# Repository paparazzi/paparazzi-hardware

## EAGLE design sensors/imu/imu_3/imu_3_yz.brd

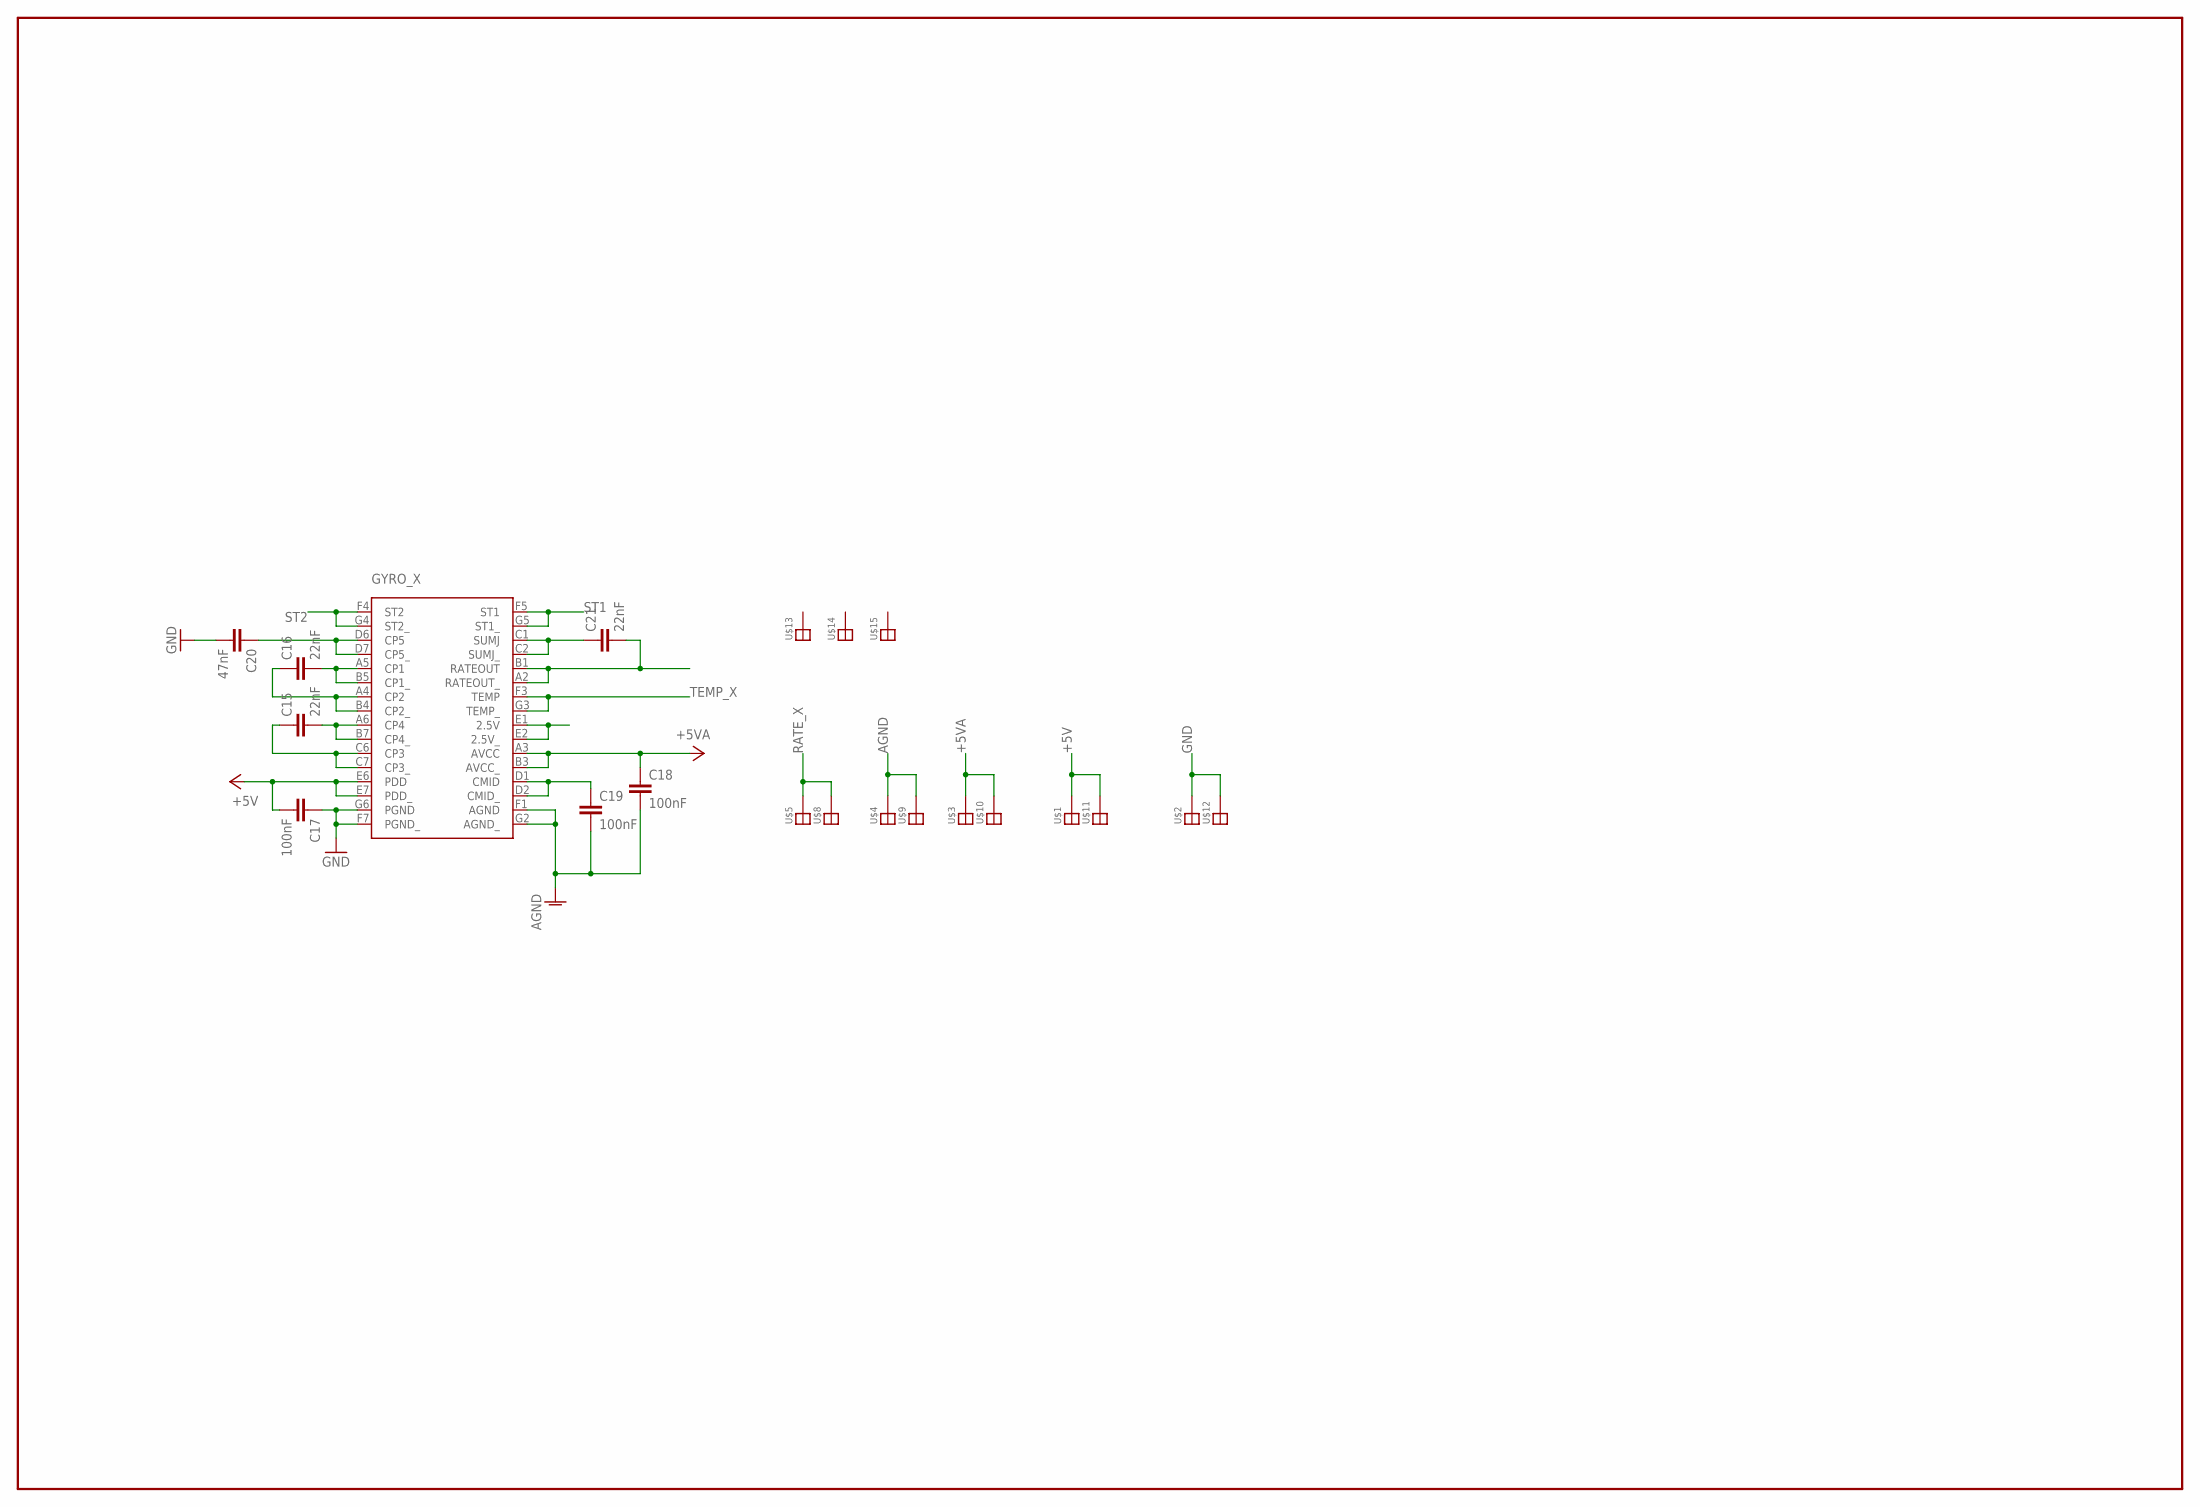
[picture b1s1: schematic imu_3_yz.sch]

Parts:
C15, C16, C21: 22nF; C0402K
C17, C18, C19: 100nF; C0402K
C20: 47nF; C0402K
GYRO_X: ADXR; BC-32
U$1, U$2, U$3, U$4, U$5, U$8, U$9, U$10, U$11, U$12, U$13, U$14, U$15: SOLDER_PAD

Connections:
+5V: C17.2, GYRO_X.E6 (PDD), GYRO_X.E7 (PDD_), U$1.P$1, U$11.P$1
+5VA: C18.1, GYRO_X.A3 (AVCC), GYRO_X.B3 (AVCC_), U$3.P$1, U$10.P$1
AGND: C18.2, C19.2, GYRO_X.F1 (AGND), GYRO_X.G2 (AGND_), U$4.P$1, U$9.P$1
GND: C17.1, C20.2, GYRO_X.F7 (PGND_), GYRO_X.G6 (PGND), U$2.P$1, U$12.P$1
unnamed: C21.1, GYRO_X.C1 (SUMJ), GYRO_X.C2 (SUMJ_)
unnamed: C15.1, GYRO_X.C6 (CP3), GYRO_X.C7 (CP3_)
unnamed: C20.1, GYRO_X.D6 (CP5), GYRO_X.D7 (CP5_)
unnamed: C16.2, GYRO_X.A5 (CP1), GYRO_X.B5 (CP1_)
unnamed: C16.1, GYRO_X.A4 (CP2), GYRO_X.B4 (CP2_)
unnamed: C15.2, GYRO_X.A6 (CP4), GYRO_X.B7 (CP4_)
unnamed: GYRO_X.E1 (2.5V), GYRO_X.E2 (2.5V_)
unnamed: C19.1, GYRO_X.D1 (CMID), GYRO_X.D2 (CMID_)
RATE_X: C21.2, GYRO_X.A2 (RATEOUT_), GYRO_X.B1 (RATEOUT), U$5.P$1, U$8.P$1
ST1: GYRO_X.F5 (ST1), GYRO_X.G5 (ST1_)
ST2: GYRO_X.F4 (ST2), GYRO_X.G4 (ST2_)
TEMP_X: GYRO_X.F3 (TEMP), GYRO_X.G3 (TEMP_)

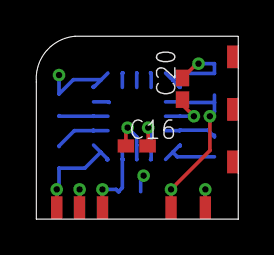
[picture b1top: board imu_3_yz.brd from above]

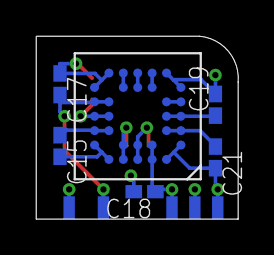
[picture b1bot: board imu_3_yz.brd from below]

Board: 4 copper layers, 11.2 x 10.2 mm, 21 parts (11 on the bottom side), 16 nets.

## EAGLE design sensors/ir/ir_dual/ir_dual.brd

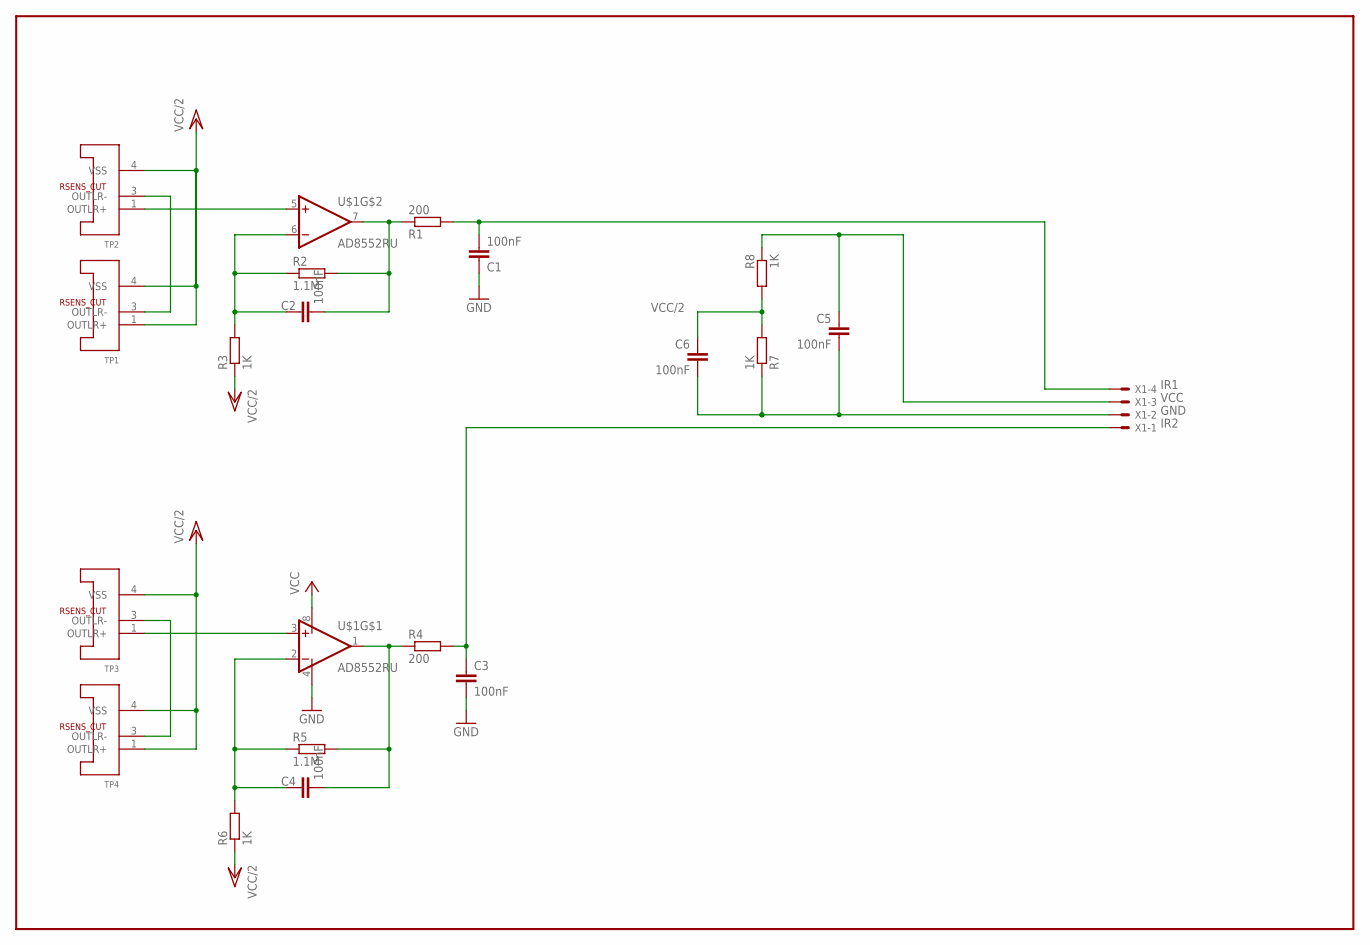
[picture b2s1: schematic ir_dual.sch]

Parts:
C1, C2, C3, C4, C5, C6: 100nF; C0603
R1, R4: 200; R0603
R2, R5: 1.1M; R0603
R3, R6, R7, R8: 1K; R0603
TP1, TP2, TP3, TP4: MLX90247; TO39H
U$1: AD8552RU; TSSOP8
X1: 53048-04

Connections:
GND: C1.1, C3.2, C5.2, C6.2, R7.1, U$1.4 (V-), X1.2
IR1: C1.2, R1.2, X1.4
IR2: C3.1, R4.2, X1.1
unnamed: TP1.3 (OUTLR-), TP2.3 (OUTLR-)
unnamed: TP3.3 (OUTLR-), TP4.3 (OUTLR-)
unnamed: TP2.1 (OUTLR+), U$1.5 (+IN)
unnamed: C2.2, R1.1, R2.2, U$1.7 (OUT)
unnamed: C2.1, R2.1, R3.2, U$1.6 (-IN)
unnamed: C4.2, R4.1, R5.2, U$1.1 (OUT)
unnamed: TP3.1 (OUTLR+), U$1.3 (+IN)
unnamed: C4.1, R5.1, R6.2, U$1.2 (-IN)
VCC: C5.1, R8.1, U$1.8 (V+), X1.3
VCC/2: C6.1, R3.1, R6.1, R7.2, R8.2, TP1.1 (OUTLR+), TP1.4 (VSS), TP2.4 (VSS), TP3.4 (VSS), TP4.1 (OUTLR+), TP4.4 (VSS)

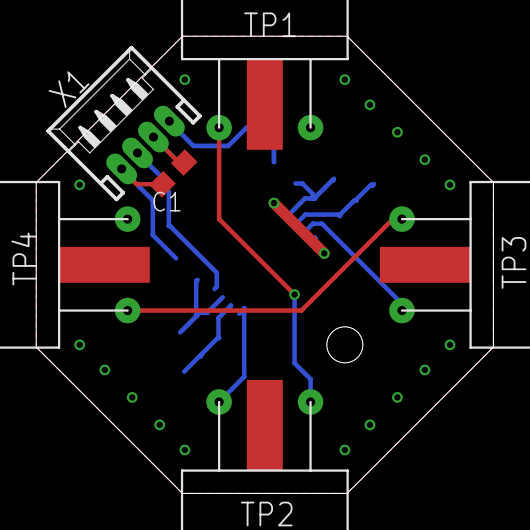
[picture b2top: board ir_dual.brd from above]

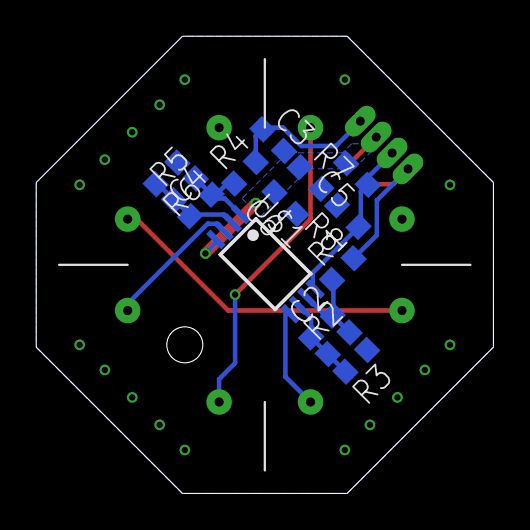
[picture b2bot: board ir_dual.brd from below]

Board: 2 copper layers, 25.4 x 25.4 mm, 20 parts (14 on the bottom side), 13 nets.

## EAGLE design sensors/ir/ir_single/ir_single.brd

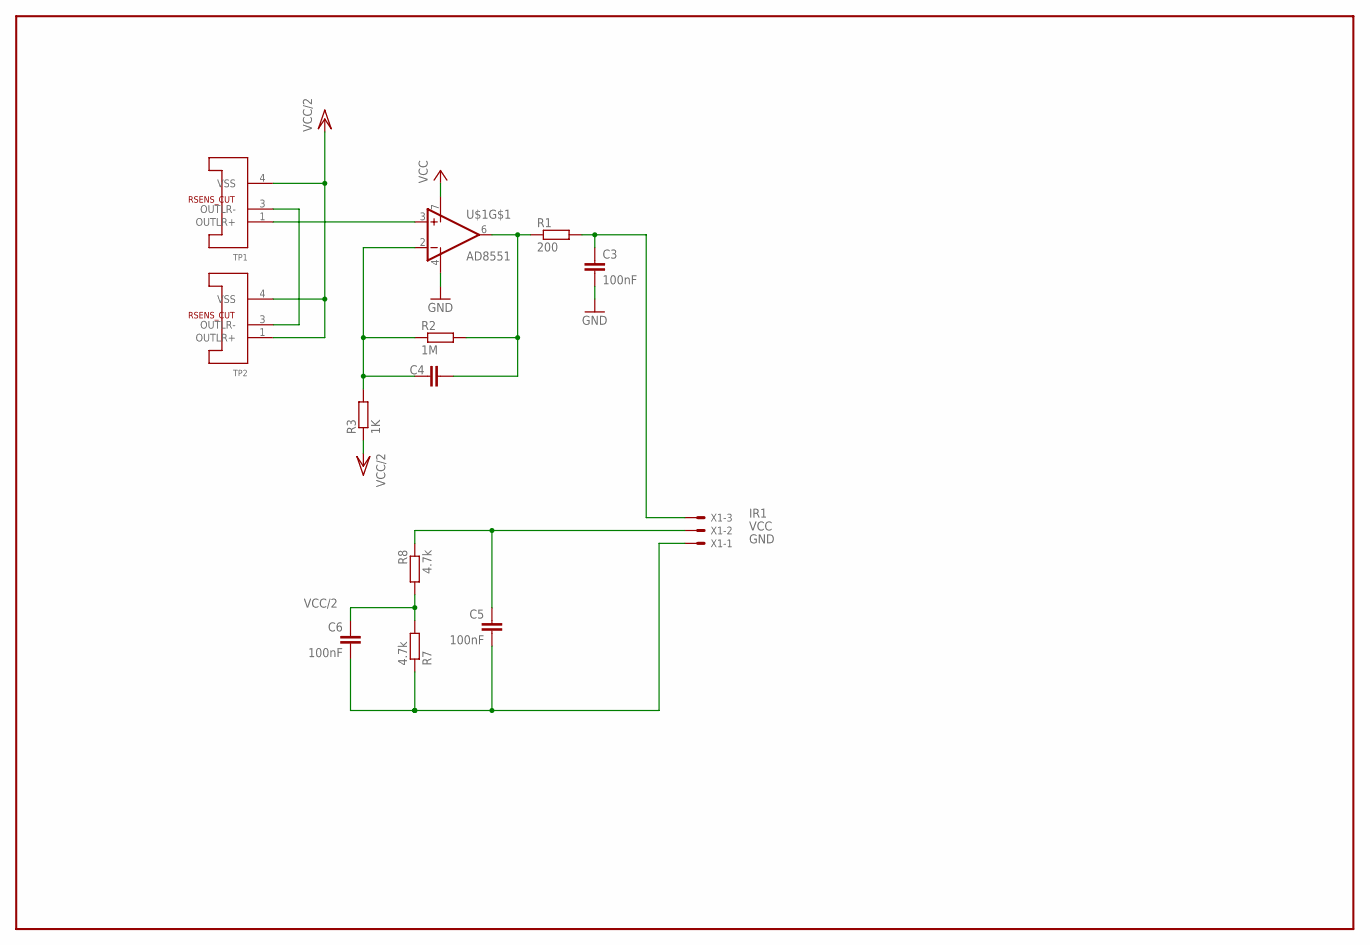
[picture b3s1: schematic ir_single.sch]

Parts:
C3, C5, C6: 100nF; C0603
C4: C-EUC0603; C0603
R1: 200; R0603
R2: 1M; R0603
R3: 1K; R0603
R7, R8: 4.7k; R0603
TP1, TP2: MLX90247; TO39H
U$1: AD8551; MSOP8
X1: 53047-03

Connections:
GND: C3.2, C5.2, C6.2, R7.1, U$1.4 (V-), X1.1
IR1: C3.1, R1.2, X1.3
unnamed: TP1.3 (OUTLR-), TP2.3 (OUTLR-)
unnamed: C4.2, R1.1, R2.2, U$1.6 (OUT)
unnamed: TP1.1 (OUTLR+), U$1.3 (+IN)
unnamed: C4.1, R2.1, R3.2, U$1.2 (-IN)
VCC: C5.1, R8.1, U$1.7 (V+), X1.2
VCC/2: C6.1, R3.1, R7.2, R8.2, TP1.4 (VSS), TP2.1 (OUTLR+), TP2.4 (VSS)

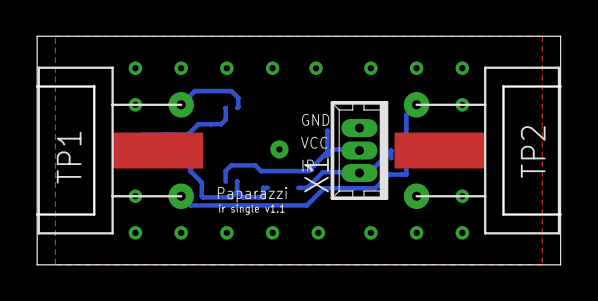
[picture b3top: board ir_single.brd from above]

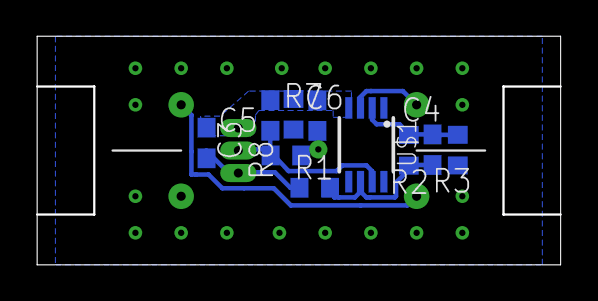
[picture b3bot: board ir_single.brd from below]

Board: 2 copper layers, 29.1 x 12.7 mm, 13 parts (10 on the bottom side), 8 nets.

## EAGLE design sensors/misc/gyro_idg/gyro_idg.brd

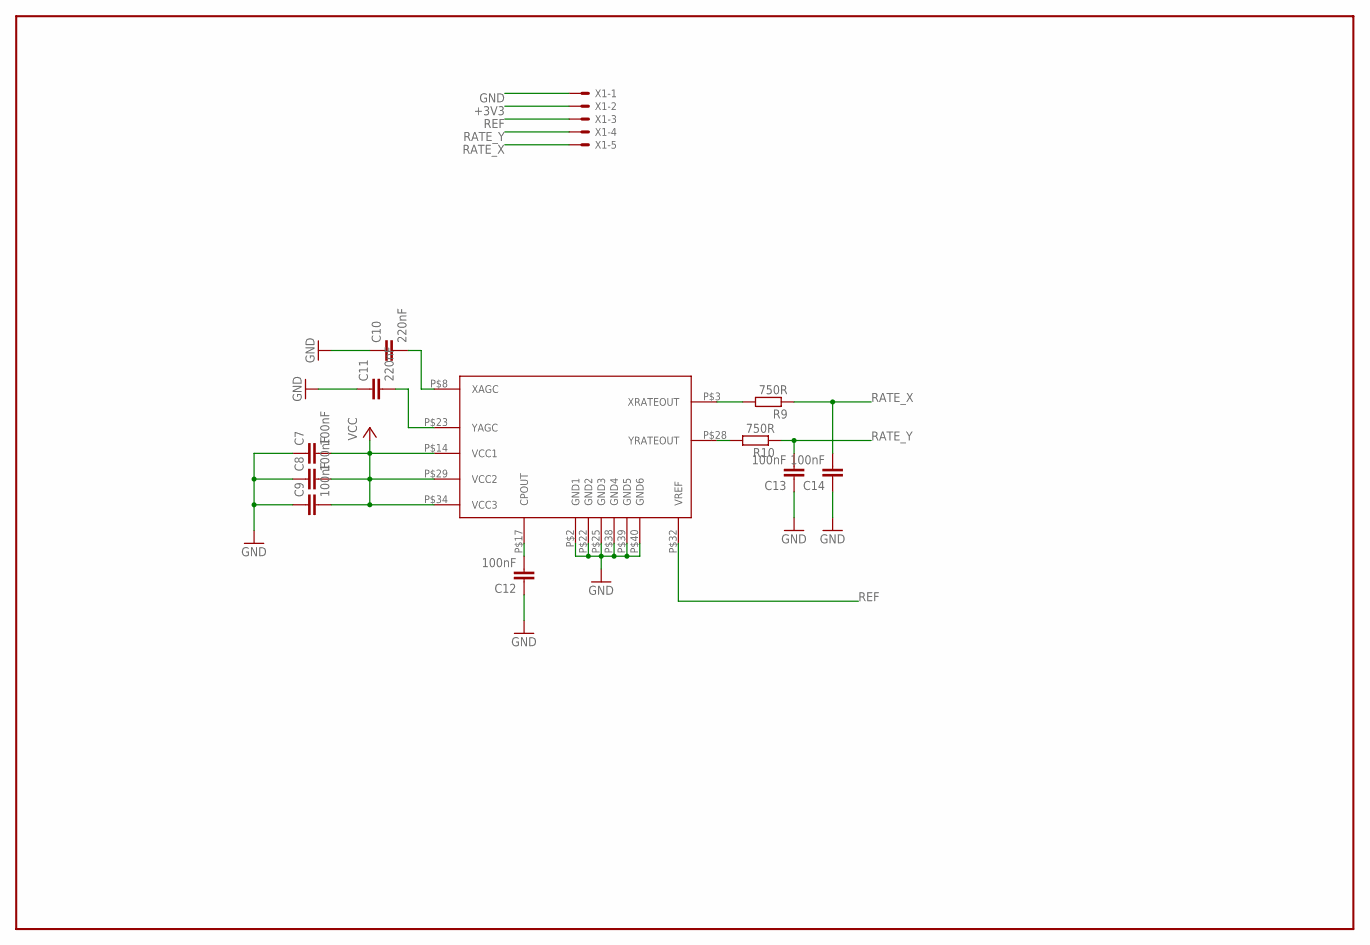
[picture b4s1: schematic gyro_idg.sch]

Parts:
C7, C8, C9, C12, C13, C14: 100nF; C0603K
C10, C11: 220nF; C0603K
R9, R10: 750R; R0603
U$2: IDG300
X1: 53047-05

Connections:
+3V3: C7.2, C8.2, C9.2, U$2.P$14 (VCC1), U$2.P$29 (VCC2), U$2.P$34 (VCC3), X1.2
GND: C7.1, C8.1, C9.1, C10.1, C11.1, C12.1, C13.1, C14.1, U$2.P$2 (GND1), U$2.P$22 (GND2), U$2.P$25 (GND3), U$2.P$38 (GND4), U$2.P$39 (GND5), U$2.P$40 (GND6), X1.1
unnamed: C11.2, U$2.P$23 (YAGC)
unnamed: C10.2, U$2.P$8 (XAGC)
unnamed: R9.2, U$2.P$3 (XRATEOUT)
unnamed: R10.2, U$2.P$28 (YRATEOUT)
unnamed: C12.2, U$2.P$17 (CPOUT)
RATE_X: C14.2, R9.1, X1.5
RATE_Y: C13.2, R10.1, X1.4
REF: U$2.P$32 (VREF), X1.3

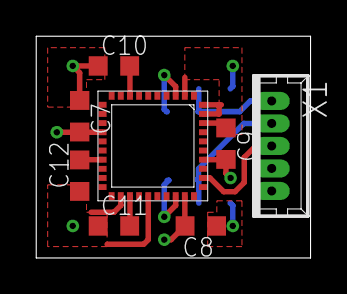
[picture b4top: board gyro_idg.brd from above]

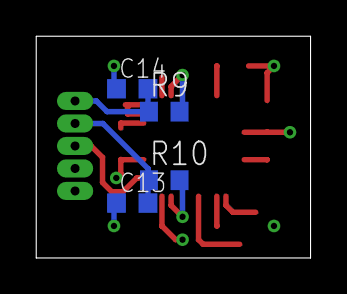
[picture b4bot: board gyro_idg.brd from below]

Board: 4 copper layers, 15.2 x 12.3 mm, 12 parts (4 on the bottom side), 10 nets.
